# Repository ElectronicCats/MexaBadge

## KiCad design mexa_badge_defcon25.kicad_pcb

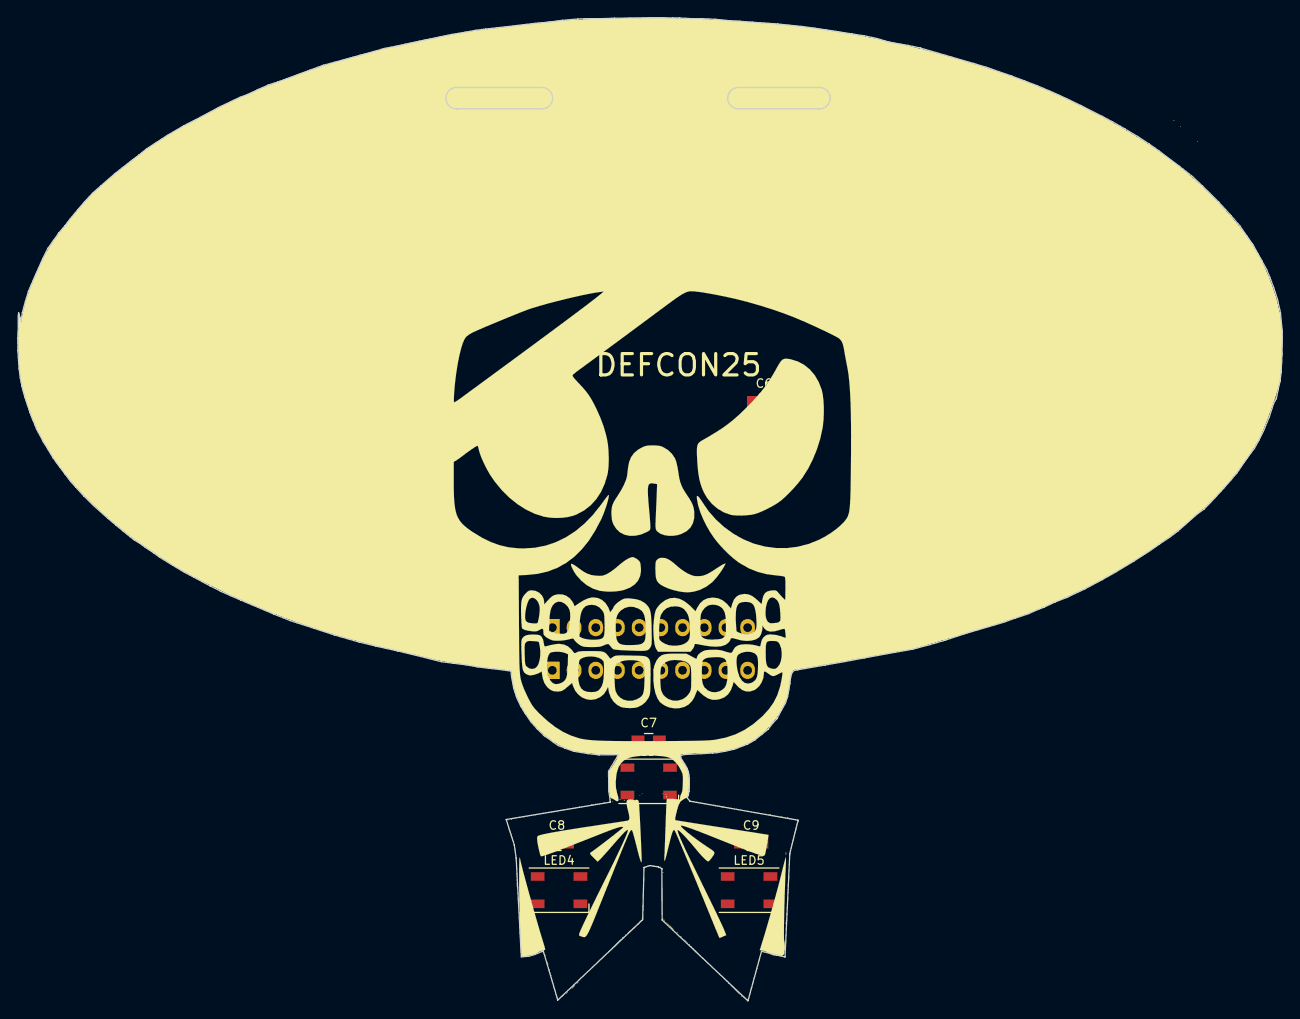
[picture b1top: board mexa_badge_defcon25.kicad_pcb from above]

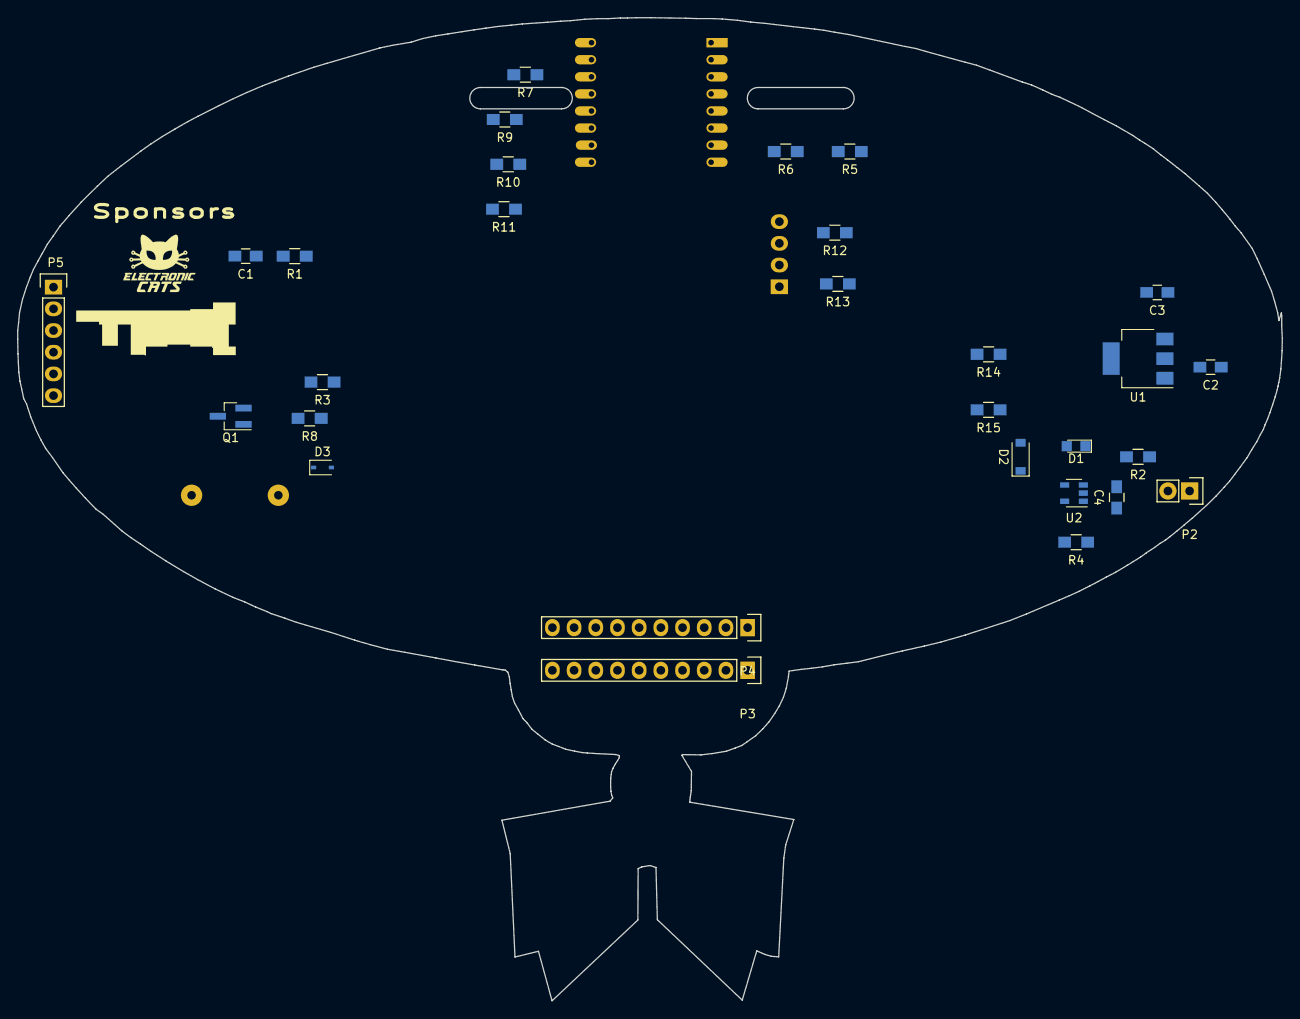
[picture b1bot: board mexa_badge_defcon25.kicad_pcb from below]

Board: 2 copper layers, 148.1 x 115.1 mm, 47 parts (29 on the bottom side), 33 nets, no tracks yet.

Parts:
BZ1: Buzzer; BUZZER
C1: 1.0uF; C_0805_HandSoldering
C2: 4.7uF; C_0805_HandSoldering
C3, C4: 10uF; C_0805_HandSoldering
C5, C6, C7, C8, C9: 0.1uF; C_0805_HandSoldering
D1: LED; LED_0805
D2: MBR120; SOD-123
D3, D5: 1N4148; SOD-323
LED1, LED2, LED3, LED4, LED5: MADW__WS2812B; LED_WS2812B-PLCC4
P2: LiPo; Socket_Strip_Straight_1x02
P3, P4: CONN_01X10; Socket_Strip_Straight_1x10
P5: USB Serial; Socket_Strip_Straight_1x06
P6: OLED_I2C; Socket_Strip_Straight_1x04
Q1: Q_PNP_BCE; SOT-23_Handsoldering
R1, R4, R9, R10, R11, R14, R15: 10K; R_0805_HandSoldering
R2, R3, R7: 1K; R_0805_HandSoldering
R5: 220K; R_0805_HandSoldering
R6: 100K; R_0805_HandSoldering
R8: 2.2K; R_0805_HandSoldering
R12, R13: 3k3; R_0805_HandSoldering
SW1: SW_RESET; SW_B3U-1000P
SW2: SW_BOOT; SW_B3U-1000P
SW3, SW4: SW_PUSH; SW_B3U-1000P
U1: SPX1117; SOT-223
U2: MCP73831; SOT-23-5
U3: ESP-12E

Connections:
+3V3: C3.1, P4.9, P6.2, R1.1, R3.1, R9.1, R10.1, R12.1, R13.1, R14.1, R15.1, U1.2, U3.8
+BATT: C4.1, C5.1, C6.1, C7.1, C8.1, C9.1, D2.2, LED1.1, LED2.1, LED3.1, LED4.1, LED5.1, P2.1, P3.1, Q1.3, U2.3
/ADC: R5.2, R6.1, U3.2
/ADC_IN: P4.3, R5.1
/CH_PD: P4.4, R10.2, U3.3
/DOUT1: LED1.2, LED5.4
/DOUT2: LED4.4, LED5.2
/DOUT3: LED2.4, LED4.2
/DOUT4: LED2.2, LED3.4
/DTR: C1.2, P5.1
/GPIO0: D3.2, P3.4, R7.2, SW2.2, U3.18
/GPIO2: P3.3, R9.2, U3.17
/GPIO4/SDA: P3.6, P6.4
/GPIO5/SCL: P3.7, P6.3
/GPIO12: P4.7, SW4.1, U3.6
/GPIO13: P4.8, SW3.1, U3.7
/GPIO14: LED1.4, P4.6, U3.5
/GPIO15: P3.2, R11.1, U3.16
/GPIO16: P4.5, R8.2, U3.4
/RST: C1.1, R1.2, SW1.1, U3.1
/RX: P3.9, P5.2, U3.22
/SCL: R12.2, U3.20
/SDA: R13.2, U3.19
/TX: D5.2, P3.8, U3.21
GND: BZ1.2, C2.2, C3.2, C4.2, C5.2, C6.2, C7.2, C8.2, C9.2, LED1.3, LED2.3, LED3.3, LED4.3, LED5.3, P2.2, P3.5, P3.10, P4.1, P4.2, P5.6, P6.1, R4.1, R6.2, R11.2, R14.2, R15.2, SW1.2, SW2.1, SW3.2, SW4.2, U1.1, U2.2, U3.15
unnamed: BZ1.1, Q1.2
unnamed: D1.1, R2.2
unnamed: D3.1, R3.2
unnamed: D5.1, P5.3
unnamed: Q1.1, R8.1
unnamed: R2.1, U2.1
unnamed: R4.2, U2.5
VCC: C2.1, D1.2, D2.1, P4.10, P5.4, U1.3, U2.4

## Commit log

2017-01-03 Add desing
2017-01-03 Coming
2017-01-03 Add Sponsors
2017-01-03 Add Schematic
2017-01-03 Update data
2017-01-03 version 0.1
2017-01-04 Change SDA and SCL
2017-01-04 Init PCB
2017-01-04 Pre acomodo
2017-01-12 fix ways
2017-01-19 Firmware based ESPTool
